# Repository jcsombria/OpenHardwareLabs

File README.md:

# OpenHardwareLabs
Open source and open hardware virtual and remote laboratories

## Introduction
This repository is a container for open-source/open-hardware remote and virtual labs.

Currently available labs:
- Air Levitation System 

# Air Levitation System

To build the air levitation system:

- Beaglebone Black board setup
  1. Verify you can boot your BBB and you have a working version of Node.js.
  2. Download and install the RIP-server (https://github.com/UNEDLabs/rip-js-server)

- Build the PCB circuit (design files are available in the folder 'AirLevitation/KiCad', and the documentation in 'AirLevitation/doc').

- Build the structure
  1. Print all the structural parts (the .stl files contained in the folder 'AirLevitation/output'). 
  2. Mount the structure and make the connections between the sensors, actuators, circuitry and beaglebone as shown in the schematic.

- EjsS
  1. Download EjsS in your PC or laptop, and open the [lab application](AirLevitation/src/EjsS) in EjsS.  
  2. Press play on EjsS to start the remote lab.

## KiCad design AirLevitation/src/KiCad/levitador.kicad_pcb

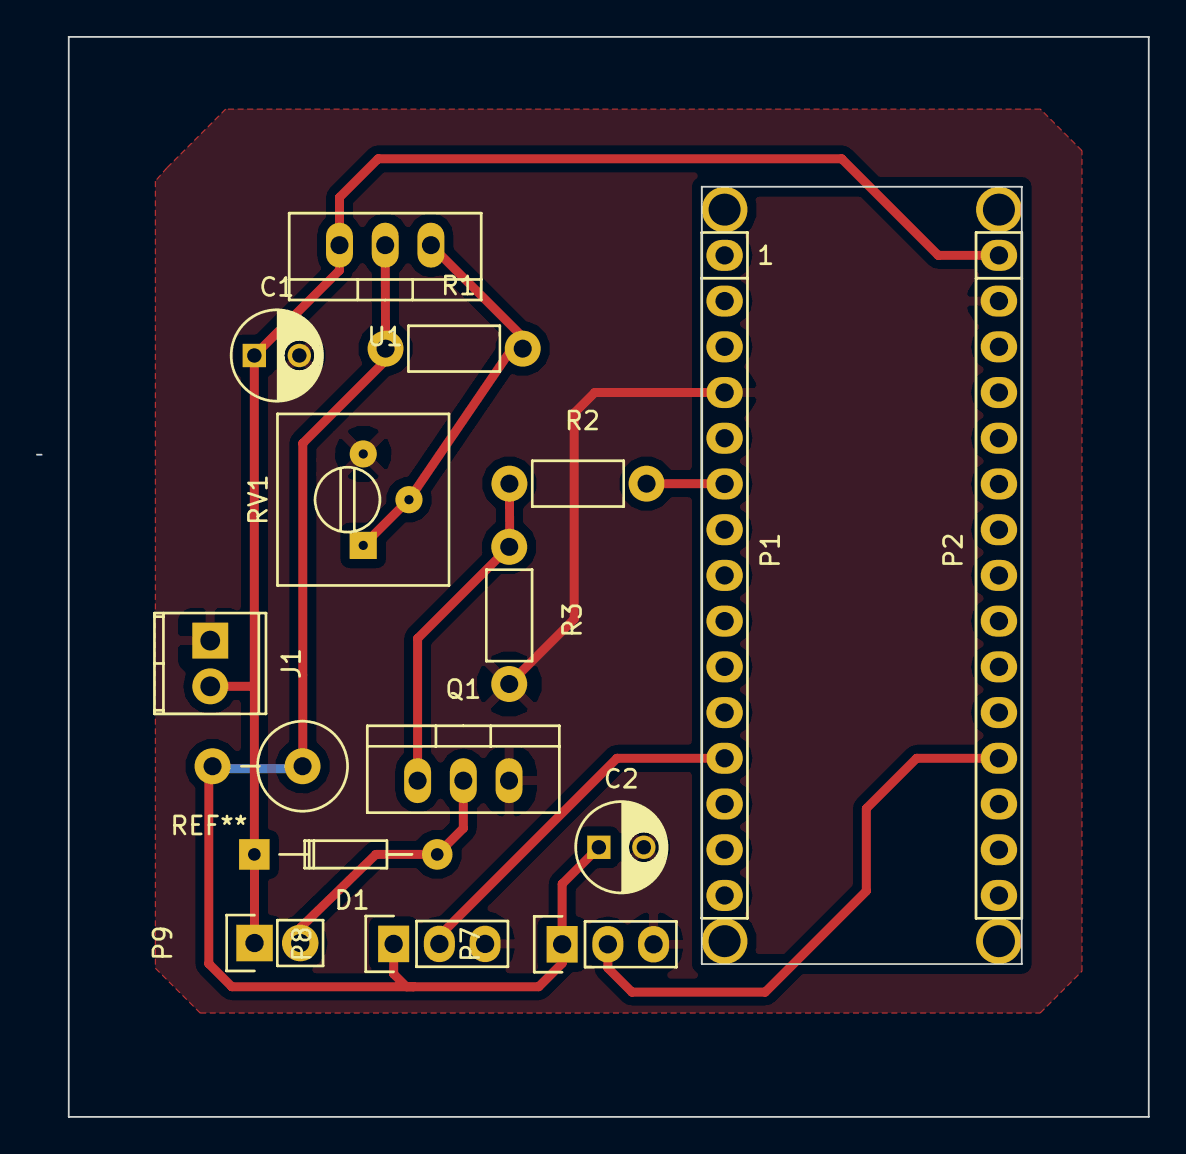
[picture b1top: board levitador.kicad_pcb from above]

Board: 2 copper layers, 61.8 x 60.0 mm, 19 parts (0 on the bottom side), 10 nets.

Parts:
C1, C2: CP; C_Radial_D5_L11_P2.5
D1: D; Diode_DO-35_SOD27_Horizontal_RM10
J1: Screw_Terminal_1x02; TerminalBlock_Pheonix_MPT-2.54mm_2pol
P1: Digital; Socket_Strip_Arduino_1x15
P2: Analog; Socket_Strip_Arduino_1x15
P3, P4, P5, P6: CONN_01X01; 1pin_Nano
P7, P8: CONN_01X03; Pin_Header_Straight_1x03
P9: CONN_01X02; Pin_Header_Straight_1x02
Q1: IRF540N; TO-220_Neutral123_Vertical
R1, R2, R3: R; Resistor_Horizontal_RM7mm
RV1: POT; Potentiometer_Trimmer-Suntan-TSR-3386P
U1: LM317AT; TO-220_Neutral123_Vertical

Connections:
+12V: C1.1, D1.1, J1.2, P2.1, P9.1, U1.3
/3(**): P1.6, R2.2
/5V: C2.1, P7.1, P8.1, R1.1, U1.2
/9(**): P1.12, P8.2
/A0: P2.12, P7.2
/OUT: D1.2, P9.2, Q1.2
/Reset: P1.3, P2.3
GND: C1.2, C2.2, J1.1, P1.4, P2.2, P7.3, P8.3, Q1.3, R3.2, RV1.3
unnamed: Q1.1, R2.1, R3.1
unnamed: R1.2, RV1.1, RV1.2, U1.1

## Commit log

2017-09-04 + Added Virtual and Remote EjsS application + Added Structural parts
2017-09-04 Added schematic and PCB
2017-09-18 Added fan cover
